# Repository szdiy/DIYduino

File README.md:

DIYduino
============
DIYduino is an Arduino compatible board.
The circuit uses DIP device, designed for beginners to learn to weld.

Schematic
------------
[PDF][schem]

BOM
------------
[CSV][bom]

PCB
------------

Photo
------------

ChangeLog
------------
[Link][changelog]

License
------------
This project is released under the CC BY-SA license.

Support
------------
dan@szdiy.org

Where to buy
------------

[schem]:https://github.com/danfei/DIYduino/raw/master/hardware/DIYduino.pdf
[bom]:https://github.com/danfei/DIYduino/raw/master/hardware/manufature/DIYduino.csv
[changelog]:https://github.com/danfei/DIYduino/blob/master/CHANGELOG.md

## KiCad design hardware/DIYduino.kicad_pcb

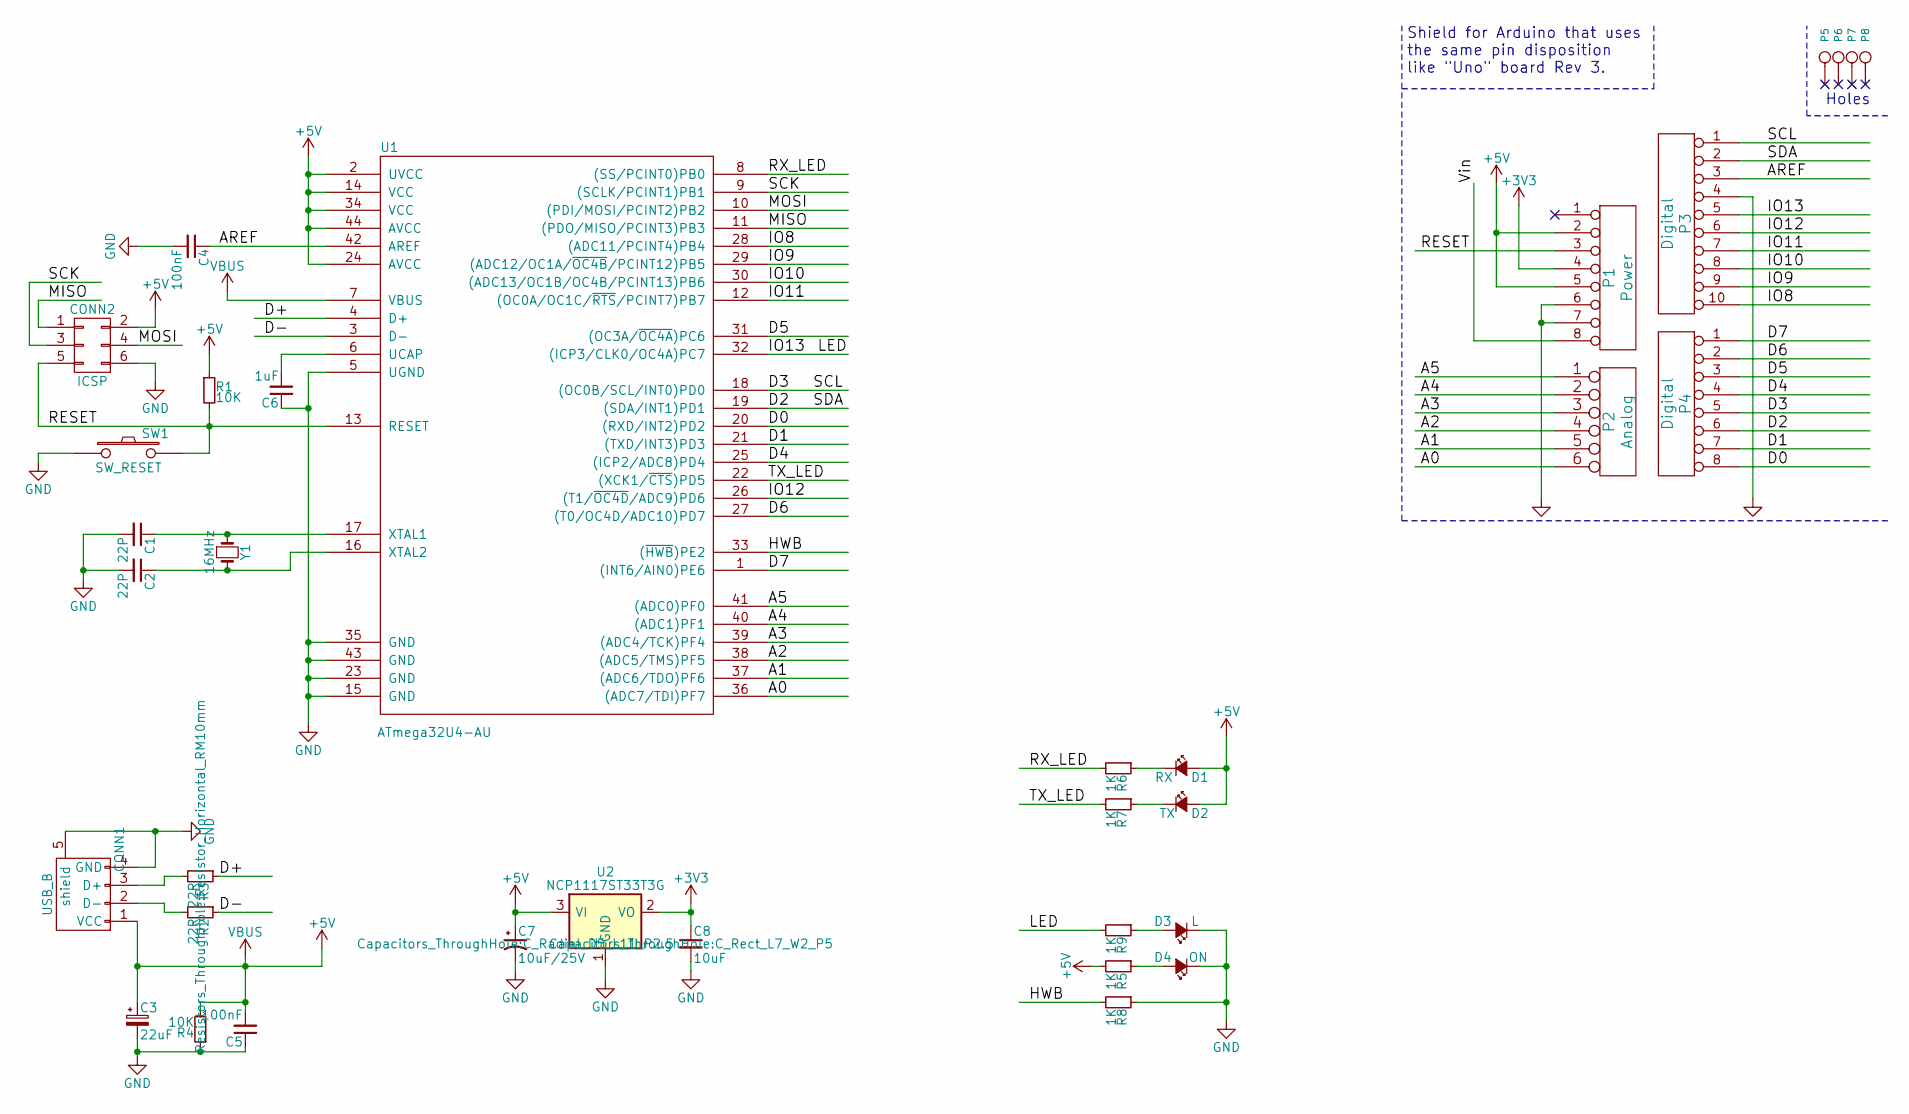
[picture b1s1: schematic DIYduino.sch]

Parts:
C1, C2: 22P; C_Rect_L7_W2_P5
C3: 22uF; C_Radial_D5_L11_P2.5
C4, C5: 100nF; C_Rect_L7_W2_P5
C6: 1uF; C_Rect_L7_W2_P5
C7: 10uF/25V; C_Radial_D5_L11_P2.5
C8: 10uF; C_Rect_L7_W2_P5
CONN1: USB_B; USB_Micro-B
CONN2: ICSP; CONN_2.54mm_2x3
D1: RX; LED-5MM
D2: TX; LED-5MM
D3: L; LED-5MM
D4: ON; LED-5MM
P1: Power; Socket_Strip_Arduino_1x08
P2: Analog; Socket_Strip_Arduino_1x06
P3: Digital; Socket_Strip_Arduino_1x10
P4: Digital; Socket_Strip_Arduino_1x08
P5, P6, P7, P8: CONN_1; Arduino_1pin
R1, R4: 10K; Resistor_Horizontal_RM10mm
R2, R3: 22R; Resistor_Horizontal_RM10mm
R5, R6, R7, R8, R9: 1K; Resistor_Horizontal_RM10mm
SW1: SW_RESET; SW_PUSH_6mm
U1: ATmega32U4-AU; TQFP-44_10x10mm_Pitch0.8mm
U2: NCP1117ST33T3G; SOT-223
Y1: 16MHz; Crystal_HC49-U_Vertical

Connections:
+3V3: C8.1, P1.4, U2.2 (VO)
+5C: C3.1, C5.2, C7.1, CONN1.1 (VCC), CONN2.2, D1.2 (A), D2.2 (A), P1.2, P1.5, R1.1, R4.2, R5.2, U1.2 (UVCC), U1.7 (VBUS), U1.14 (VCC), U1.24 (AVCC), U1.34 (VCC), U1.44 (AVCC), U2.3 (VI)
/A0: P2.6, U1.36 ((ADC7/TDI)PF7)
/A1: P2.5, U1.37 ((ADC6/TDO)PF6)
/A2: P2.4, U1.38 ((ADC5/TMS)PF5)
/A3: P2.3, U1.39 ((ADC4/TCK)PF4)
/A4: P2.2, U1.40 ((ADC1)PF1)
/A5: P2.1, U1.41 ((ADC0)PF0)
/AREF: C4.1, P3.3, U1.42 (AREF)
/D0: P4.8, U1.20 ((RXD/INT2)PD2)
/D1: P4.7, U1.21 ((TXD/INT3)PD3)
/D2: P3.2, P4.6, U1.19 ((SDA/INT1)PD1)
/D3: P3.1, P4.5, U1.18 ((OC0B/SCL/INT0)PD0)
/D4: P4.4, U1.25 ((ICP2/ADC8)PD4)
/D5: P4.3, U1.31 ((OC3A/~OC4A~)PC6)
/D6: P4.2, U1.27 ((T0/OC4D/ADC10)PD7)
/D7: P4.1, U1.1 ((INT6/AIN0)PE6)
/D+: R3.1, U1.4 (D+)
/D-: R2.1, U1.3 (D-)
/HWB: R8.2, U1.33 ((~HWB~)PE2)
/IO8: P3.10, U1.28 ((ADC11/PCINT4)PB4)
/IO9: P3.9, U1.29 ((ADC12/OC1A/~OC4B~/PCINT12)PB5)
/IO10: P3.8, U1.30 ((ADC13/OC1B/OC4B/PCINT13)PB6)
/IO11: P3.7, U1.12 ((OC0A/OC1C/~RTS~/PCINT7)PB7)
/IO12: P3.6, U1.26 ((T1/~OC4D~/ADC9)PD6)
/IO13: P3.5, R9.2, U1.32 ((ICP3/CLK0/OC4A)PC7)
/MISO: CONN2.1, U1.11 ((PDO/MISO/PCINT3)PB3)
/MOSI: CONN2.4, U1.10 ((PDI/MOSI/PCINT2)PB2)
/RESET: CONN2.5, P1.3, R1.2, SW1.2, U1.13 (RESET)
/RX_LED: R6.2, U1.8 ((SS/PCINT0)PB0)
/SCK: CONN2.3, U1.9 ((SCLK/PCINT1)PB1)
/TX_LED: R7.2, U1.22 ((XCK1/~CTS~)PD5)
/Vin: P1.8
GND: C1.2, C2.2, C3.2, C4.2, C5.1, C6.1, C7.2, C8.2, CONN1.4 (GND), CONN1.5 (shield), CONN2.6, D3.1 (K), D4.1 (K), P1.6, P1.7, P3.4, R4.1, R8.1, SW1.1, U1.5 (UGND), U1.15 (GND), U1.23 (GND), U1.35 (GND), U1.43 (GND), U2.1 (GND)
unnamed: C1.1, U1.17 (XTAL1), Y1.1
unnamed: C2.1, U1.16 (XTAL2), Y1.2
unnamed: C6.2, U1.6 (UCAP)
unnamed: CONN1.2 (D-), R2.2
unnamed: CONN1.3 (D+), R3.2
unnamed: D1.1 (K), R6.1
unnamed: D2.1 (K), R7.1
unnamed: D3.2 (A), R9.1
unnamed: D4.2 (A), R5.1

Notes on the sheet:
Holes
Shield for Arduino that uses the same pin disposition like "Uno" board Rev 3.

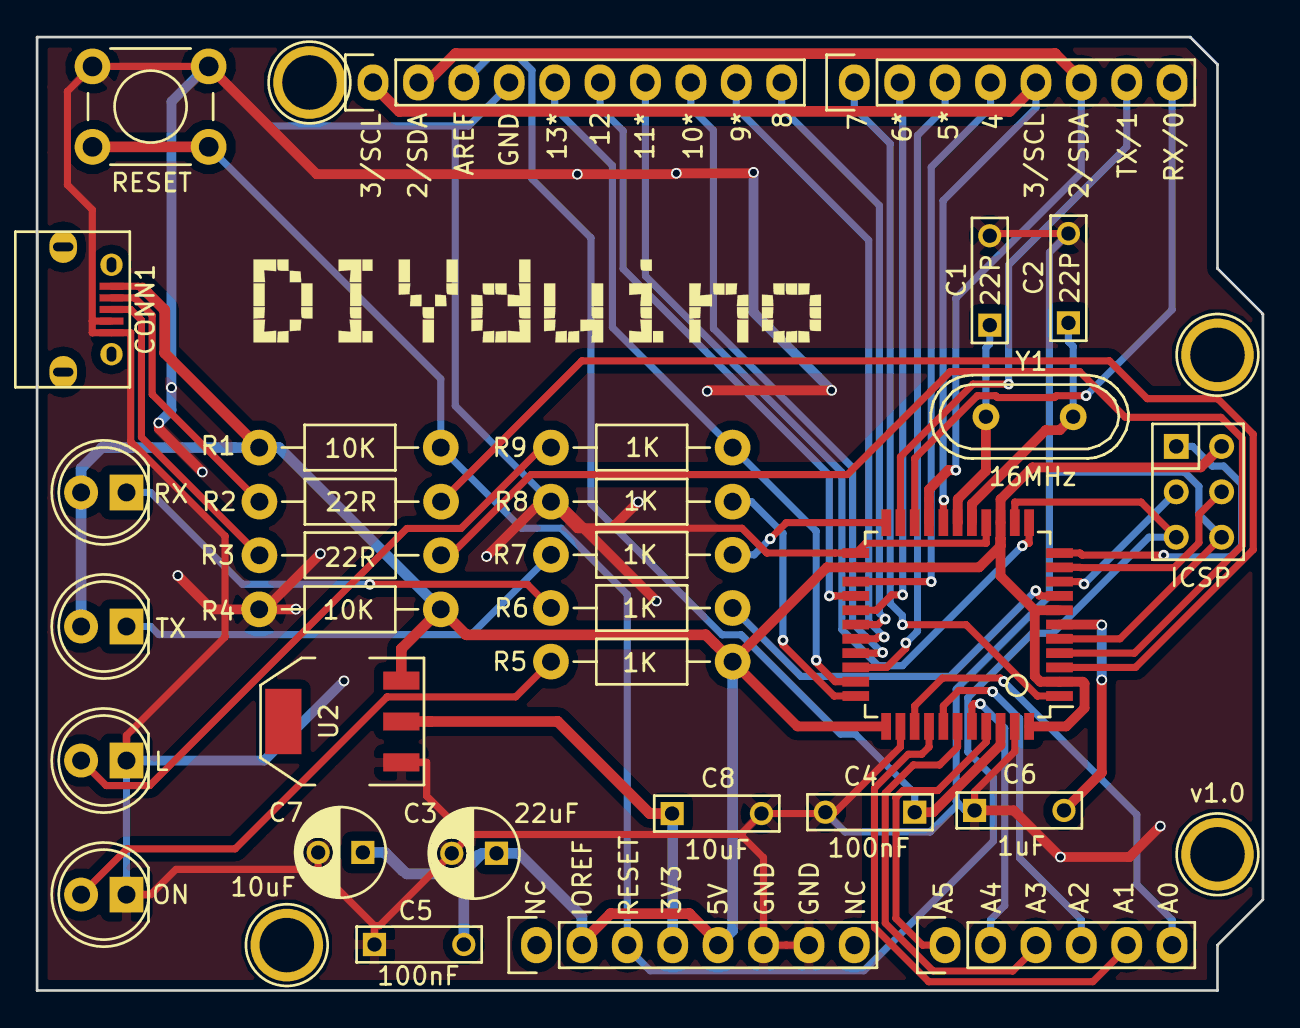
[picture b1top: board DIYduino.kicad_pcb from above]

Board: 2 copper layers, 68.6 x 53.3 mm, 35 parts (0 on the bottom side), 42 nets.

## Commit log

2016-12-23 alpha version
2016-12-23 Beta version
2016-12-23 readme
2016-12-25 Modified silk layer
2016-12-25 Added screenshots and BOM file
2016-12-25 Updated changelog
2016-12-26 rename
2016-12-26 rm logo
2016-12-28 Updated schem pdf
2016-12-29 remove LICENSE.md
2017-01-01 rm sth
